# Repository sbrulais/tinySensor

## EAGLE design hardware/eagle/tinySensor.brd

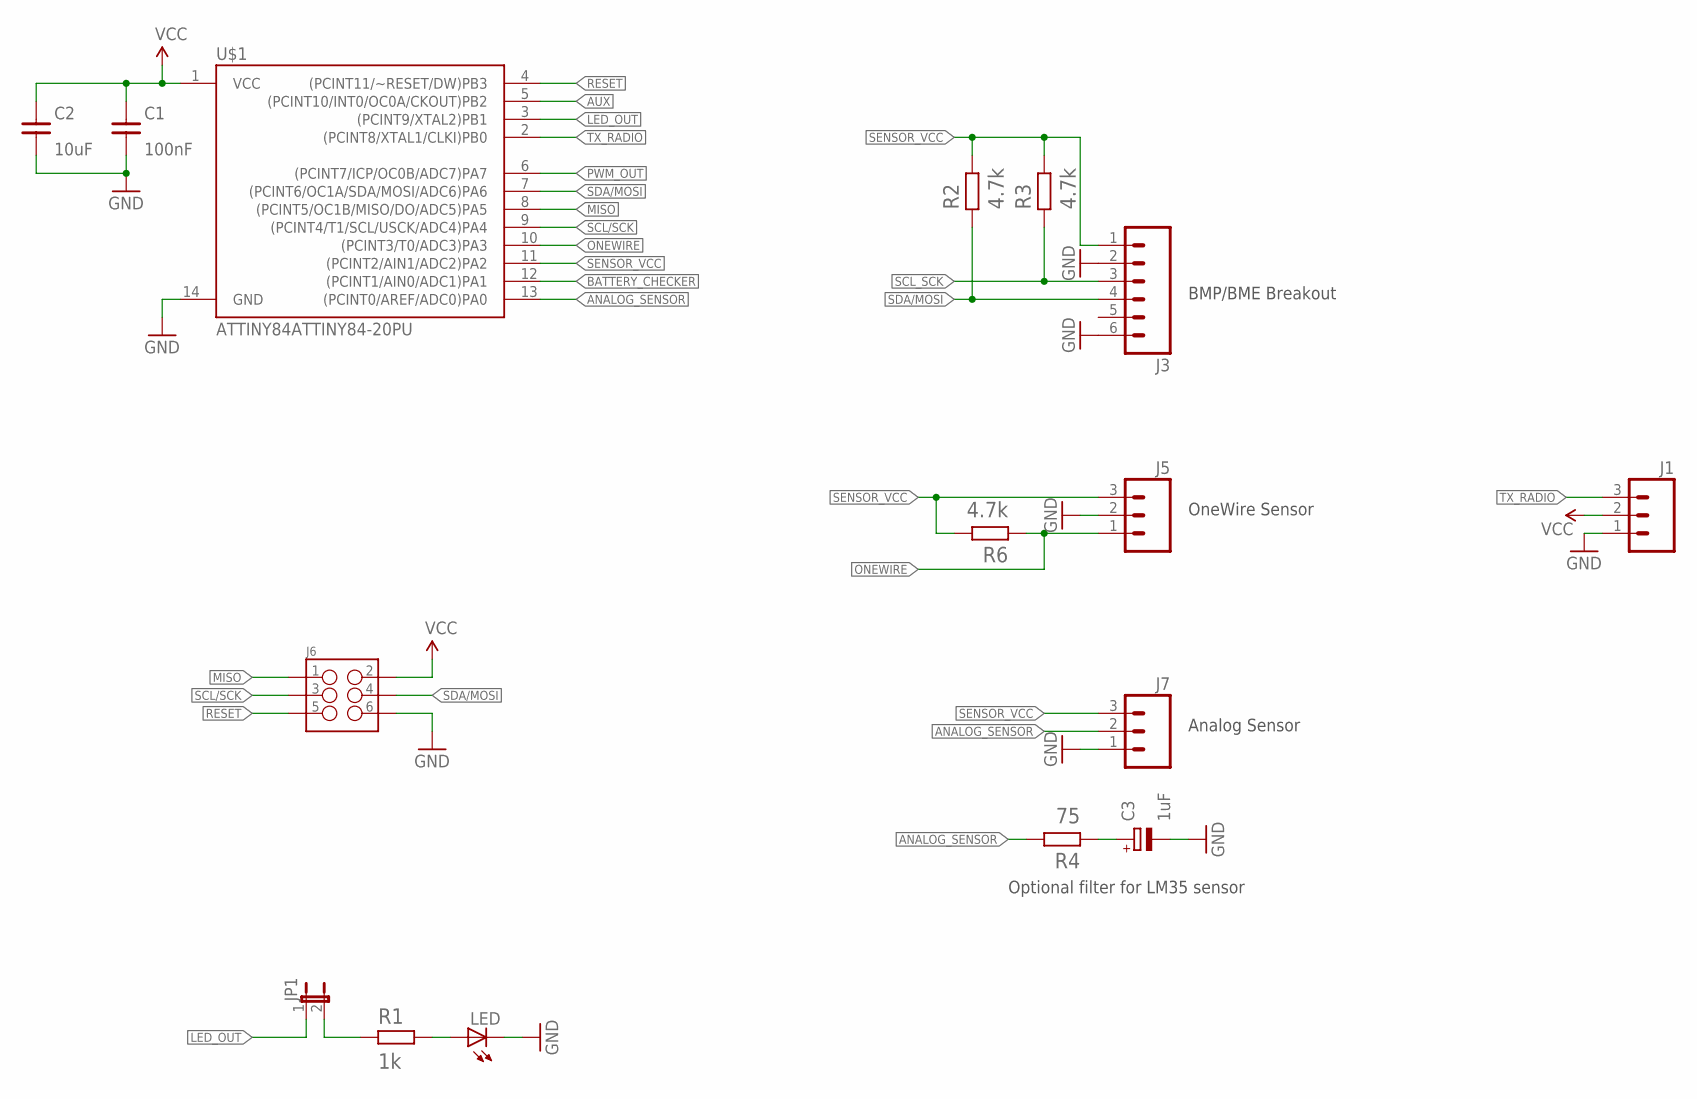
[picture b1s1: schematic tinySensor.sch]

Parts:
C1: 100nF; R0805
C2: 10uF; R0805
C3: 1uF; PANASONIC_C
J1, J5, J7: M03PTH; 1X03
J3: M06SIP; 1X06
J6: M03X2SHROUD; 2X3-SHROUDED
JP1: JUMPER-2PTH; 1X02
LED: LED3MM
R1: 1k; R0805
R2, R3, R6: 4.7k; R0805
R4: 75; R0805
U$1: ATTINY84ATTINY84-20PU; DIL14

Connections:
ANALOG_SENSOR: J7.2, R4.2, U$1.13 ((PCINT0/AREF/ADC0)PA0)
AUX: U$1.5 ((PCINT10/INT0/OC0A/CKOUT)PB2)
BATTERY_CHECKER: U$1.12 ((PCINT1/AIN0/ADC1)PA1)
GND: C1.1, C2.1, C3.-, J1.1, J3.2, J3.6, J5.2, J6.6, J7.1, LED.K (C), U$1.14 (GND)
LED_OUT: JP1.1, U$1.3 ((PCINT9/XTAL2)PB1)
MISO: J6.1, U$1.8 ((PCINT5/OC1B/MISO/DO/ADC5)PA5)
unnamed: JP1.2, R1.1
unnamed: LED.A, R1.2
unnamed: C3.+, R4.1
ONEWIRE: J5.1, R6.1, U$1.10 ((PCINT3/T0/ADC3)PA3)
PWM_OUT: U$1.6 ((PCINT7/ICP/OC0B/ADC7)PA7)
RESET: J6.5, U$1.4 ((PCINT11/~RESET/DW)PB3)
SCL/SCK: J6.3, U$1.9 ((PCINT4/T1/SCL/USCK/ADC4)PA4)
SCL_SCK: J3.3, R3.1
SDA/MOSI: J3.4, J6.4, R2.1, U$1.7 ((PCINT6/OC1A/SDA/MOSI/ADC6)PA6)
SENSOR_VCC: J3.1, J5.3, J7.3, R2.2, R3.2, R6.2, U$1.11 ((PCINT2/AIN1/ADC2)PA2)
TX_RADIO: J1.3, U$1.2 ((PCINT8/XTAL1/CLKI)PB0)
VCC: C1.2, C2.2, J1.2, J6.2, U$1.1 (VCC)

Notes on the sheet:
BMP/BME Breakout
Analog Sensor
OneWire Sensor
Optional filter for LM35 sensor

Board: 2 copper layers, 16 parts (3 on the bottom side), 15 nets, no tracks yet.

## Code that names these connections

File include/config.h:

/*
 * This file is part of the TinySensor distribution (https://github.com/arcadien/TinySensor)
 *
 * Copyright (c) 2019 Aurélien Labrosse
 *
 * This program is free software: you can redistribute it and/or modify
 * it under the terms of the GNU General Public License as published by
 * the Free Software Foundation, version 3.
 *
 * This program is distributed in the hope that it will be useful, but
 * WITHOUT ANY WARRANTY; without even the implied warranty of
 * MERCHANTABILITY or FITNESS FOR A PARTICULAR PURPOSE. See the GNU
 * General Public License for more details.
 *
 * You should have received a copy of the GNU General Public License
 * along with this program. If not, see <http://www.gnu.org/licenses/>.
 */

#pragma once

#include <inttypes.h>

// sleep 32s between each sample and
// emission
#define SLEEP_TIME_IN_SECONDS (8 * 4)

#define LED_PIN PB1
#define PWM_PIN PA7
#define TX_RADIO_PIN PB0
#define RADIO_POWER_PIN PA2
#define BAT_SENSOR_PIN PA1


/* 
* actual value for 1v1 internal ref,
* which have to be checked for each MCU
* \see https://provideyourown.com/2012/secret-arduino-voltmeter-measure-battery-voltage/
*
*
* Briefly, the reference can be obtained by 
* `internal1.1Ref = 1.1 * Vcc1 (per voltmeter) / Vcc2 (per readVcc() function)`
*/
#define ACTUAL_1V1_REF_MV 1100.

#ifdef BOARD_USES_3V3_STEPUP
#define ACTUAL_VCC_MV 3280.
#else
#define ACTUAL_VCC_MV readVcc()
#endif

// Sensors
#define USE_BMP280
//#define USE_BME280
//#define USE_DS18B20

#if defined(USE_BMP280) or defined(USE_BME280)
#define USE_I2C
#endif

const uint8_t OREGON_ID = SENSOR_ID;
const uint8_t OREGON_TYPE[] = SENSOR_TYPE;

/*
 * MODE_0 0 // Temperature only [THN132N]
 * MODE_1 1 // Temperature + Humidity [THGR2228N]
 * MODE_2 2 // Temperature + Humidity + Baro() [BTHR918N]
 */
// #define OREGON_MODE MODE_1

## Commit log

2020-01-20 new form
2020-02-09 feat: Now able to sense and emit battery level
    * VBatt voltage is sent using the X10 protocol
2020-02-16 feat: Last enhancements from hardware testing
    * Full LM35 support: <0 temp with diode support
    * 433Mhz emitter is powered by SENSOR_VCC
    * Enhanced layout
2020-02-20 layout enhancements
2020-02-24 feat: Allow shutdown of DCDC stepup
2021-04-30 Created eagle project
2021-04-30 Schematics redrawn, work in progress

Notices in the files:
parts and their libraries:
SparkFun-DigitalIC: Licensing: Creative Commons ShareAlike 4.0 International - https://creativecommons.org/licenses/by-sa/4.0
